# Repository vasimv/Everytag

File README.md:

# Everytag
The firmware emulates Apple Airtag (up to 40 public keys rotating at default 10 minutes interval) and Google Find My Device (just one non-rotating key at the moment). It works on nRF52/54 chips and uses Zephyr. I've tried to optimize power consumption as much as could (microamperes range). MCU's watchdog is used to be sure it always works until battery dies.

One of biggest advantages of the firmware is ability to reconfigure all of its settings via BLE (python script is included), so you can change keys, transmitting power, broadcasting interval and such without reflashing. To minimize power consumption, the firmware accepts connections to change settings only for 2 seconds every minute and has simple password protection.

As beta test feature, it counts current time (if your board has 32.768kHz crystal) and saves current time to the flash periodically, so clock won't drift too much even if it gets reboot.

Also, it is possible to do OTA firmware update on nRF52/54 chips with at least 512KB flash/RRAM memory through mcumgr protocol. That includes nRF52832 (512KB version), nRF52833, nRF54L15. OTA won't work on nRF52805, nRF52810 but you can still change settings through BLE.

## Credits and useful links
Big thanks to OpenHaystack project for their great work: https://github.com/seemoo-lab/openhaystack

The firmware originated as a fork of macless-haystack project and has some of its code: https://github.com/dchristl/macless-haystack

To query locations you can use FindMy scripts: https://github.com/biemster/FindMy

To create Google FMDN key and query locations, use this: https://github.com/leonboe1/GoogleFindMyTools

## Hardware

The firmware has support (see boards/ subdirectory) and tested on these boards and beacons: NRF52DK (nRF52832), NRF54L15DK (nRF54L15), KKM C2 (nRF52805), KKM K4P (K5) with accelerometer (nRF52833), KKM P1 (nRF52810), KKM P11 (nRF52810), Fanstel NRF52805EVM (nRF52805), Minew HCB22E (nRF52832). For NRF52DK, KKM C2 and KKM K4P you will have to use button to turn it on after first flash. On other boards/beacons it'll start right after flashing. Only one LED will blink on the start (1 short, 2 long).

Button (first one on NRF52DK board) can be used to turn off/on. Long press the button until 1 short + 2 long LED flashes to start it on. Same long press for shutdown, it'll do two short flashes and issue sys_poweroff(), less than one microampere in that state. Power on/off status is stored into flash, so it'll stay same after battery replacement (will blink once after installing new battery and return to sleep if was turned off).

Additionally, i've included my design of beacon that has Qi/WPC wireless charging support (nRF52833, BQ51013B, BQ25121A), see hardware/ subdirectory. The goal was to make small and very thin beacon (50x20x2mm with LIR2016 li-ion battery). You can order these assembled on PCBWay https://www.pcbway.com/project/shareproject/Small_and_thin_50x20x2mm_Bluetooth_beacon_with_Qi_WPC_wireless_charging_f97170e6.html (around 35 USD per board).

## Compilation
Zephyr-based nRF Connect SDK 2.8.0 is required to compile the firmware.

myboards.h file has compilation-time settings (like how often switch to settings mode, etc). 

In the Visual Studio Code - click on nrfconnect plugin button, create build configuration for your board. Use following configuration files:

prj-smpsrv.conf - debug (through J-Link RTT interface) version with mcumgr support (for 512KB or bigger flash chips). You can use JlinkRTTViewer to connect and see debug messages on its console.

prj-smpsrv-lowpower.conf - no debug version for lowest power consumption and memory usage, with mcumgr support

prj.conf - debug version without mcumgr support (no mcuboot) for small memory chips - nRF52805, nRF52810, nRF52811

prj-lowpower.conf - no debug version for these chips

For nRF52DK/nrf52832 and nRF54L15DK - use nrf52832dk.overlay / nrf54l15dk.overlay files as "Extra Devicetree overlays"

## Running
It is recommended to erase all flash memory before first run to reset NVS storage where the firmware stores its settings.

Disconnect power source (remove battery) for 10-20 seconds and reconnect again after flashing through SWD or using RTT debug console, nrf chips often switch to high power consumption (up to few milliamps range) after using Jlink RTT interface and software reset doesn't help. So far, i haven't found way to avoid that.

By default, the firmware will start broadcasting dummy iBeacon packets with 7 seconds interval at very low power (-8dBm) with TX power field set as battery voltage (like 31 is 3.1 volts). This broadcast will stop as soon as you load Apple Airtag and/or Google FMDN key.

The beacon will use default MAC address (from MCU's registers programmed at factory) for iBeacon and settings broadcasts. You can figure out the address via debug console or using an BLE scanning app (nrfconnect from Nordic is quite good and free) on a smartphone.

## Changing settings via BLE
Every minute it will switch into settings mode for 2 seconds (configurable) and settings (including keys) can be changed by conn_beacon.py script (requires python 3) or by using android application that AI did generate for me (see below). Note, bluez isn't really perfect stack to work with BLE and the script may have troubles while connecting to the beacon. To fix that, you may try to disable/enable bluetooth or even reboot your computer.

The script is used for:
1. Changing its settings and/or writing current time to the beacon
2. Reading current time from the beacon
3. Switching the beacon into mcumgr OTA mode for one minute

All of these requires password authentication (default password is "abcdefgh", can be changed via settings mode too)

Note, after loading an Airtag key, MAC address in settings mode will be changed, it is recommended to set a specific MAC address for the settings mode when loading an Airtag key. Otherwise, you will have to figure out current MAC address via nrfconnect app or in a similar way.

Examples:
`python3 conn_beacon.py -i e7:93:3a:cc:f6:61 -c e7:93:3a:cc:f6:61 -a abcdefgh -n h45edc78 -f f1e101731f1e1b312272f812e521293a3f484414 -k ~/airtags/016WX1_keyfile -p 2 -g 1 -t 1 -w 1 -d 2`

This will connect to beacon with E7:93:3A:CC:F6:61 MAC address, change password to "h45edc78" load airtag key from 016WX1_keyfile, load FMDN key "f1e101731f1e1b312272f812e521293a3f484414", set maximum TX power (+4 or +8 dBm), allow broadcasting both Airtag and FMDN, switching every 2 seconds. You can omit some settings you don't want to change, only MAC address (-i) and authorization code (-a) is required.

`python3 conn_beacon.py -i e7:93:3a:cc:f6:61 -a h45edc78 -w 1`

This will connect to the beacon and synchronize its clock to current time.

`python3 conn_beacon.py -i e7:93:3a:cc:f6:61 -a h45edc78 -r 1`

This will connect to the beacon and read current time

To use OTA update feature, see flash_beacon.sh and flash_list.sh. Debug/lowpower versions of the mcumgr stuff may be uncompatible between each other, so you may get troubles with reflashing over bluetooth if flashed wrong version first. Settings are stored in separate region of flash/RRAM and they will be same after OTA, use full chip erase through SWD to get rid of old settings or use conn_beacon.py to program new ones.

## Using android application to change settings
Check subdirectory tagcheck for the android application. I have around zero knowledge about the android application development, so ChatGPT did wrote it for me. Sorry for its general ugliness, i'm not an UI guy. This is AndroidStudio project and you can compile it by yourself or use apk included.

"SCAN BLE" functionality will find all BLE stuff with RSSI is bigger than specififed value. This will help to find MAC address of your beacon (place it very close to the phone's bluetooth antenna, so RSSI will be bigger). You can tap on one of scanned results to fill target's MAC address to send settings instead of typing MAC manually.

On settings screen you can choose which settings to update on the Everytag beacon by activating their respective checkboxes. You have to set target MAC address and password (authorization code) to be able to reconfigure beacon. You will need to upload an airtag keyfile to the phone to change its broadcast key.

"Firmware Update" will upgrade firmware through BLE, you have to upload zephyr.signed.bin to your phone first.

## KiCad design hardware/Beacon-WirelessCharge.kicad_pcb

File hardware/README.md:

## Bluetooth beacon design with Qi/WPC charging

The goal of the project was to make thin and small BLE beacon that uses Li-Ion battery and can be recharged with wireless charging. Note, it may not work with all Qi/WPC chargers because small receiving charging coil, it is highly recommended to adapt charger by replacing its transmitting coil with small 20mm diameter coil. I've used Wurth 760308101104 coil with Adafruit 2162 Qi/WPC charger module.

Final size with LIR2016 battery - 50x20x2mm in thin variant. If height is not limited, then battery can be placed above the board and size will be 30x20mm. A ferrite gasket 20x15mm plate is strongly recommended to be glued on the receiving coil, i've used Wurth 74274119 in that role. 5x1mm round magnet can be placed in the hole on the board and transmitting antenna, so both coils will self-align while charge.

When placed on a Qi/WPC charger - reset pulse will be generated for the MCU, keep that in mind if you want to use with your own firmwares. BQ25121A is used in I2C-only configuration to simplify PCB design, you have to configure charging current, voltages and such during MCU initialization.

BQ25121A and 0402 sized components are quite hard to solder manually, so you may want to order them assembled! Link on PCBWay: https://www.pcbway.com/project/shareproject/Small_and_thin_50x20x2mm_Bluetooth_beacon_with_Qi_WPC_wireless_charging_f97170e6.html

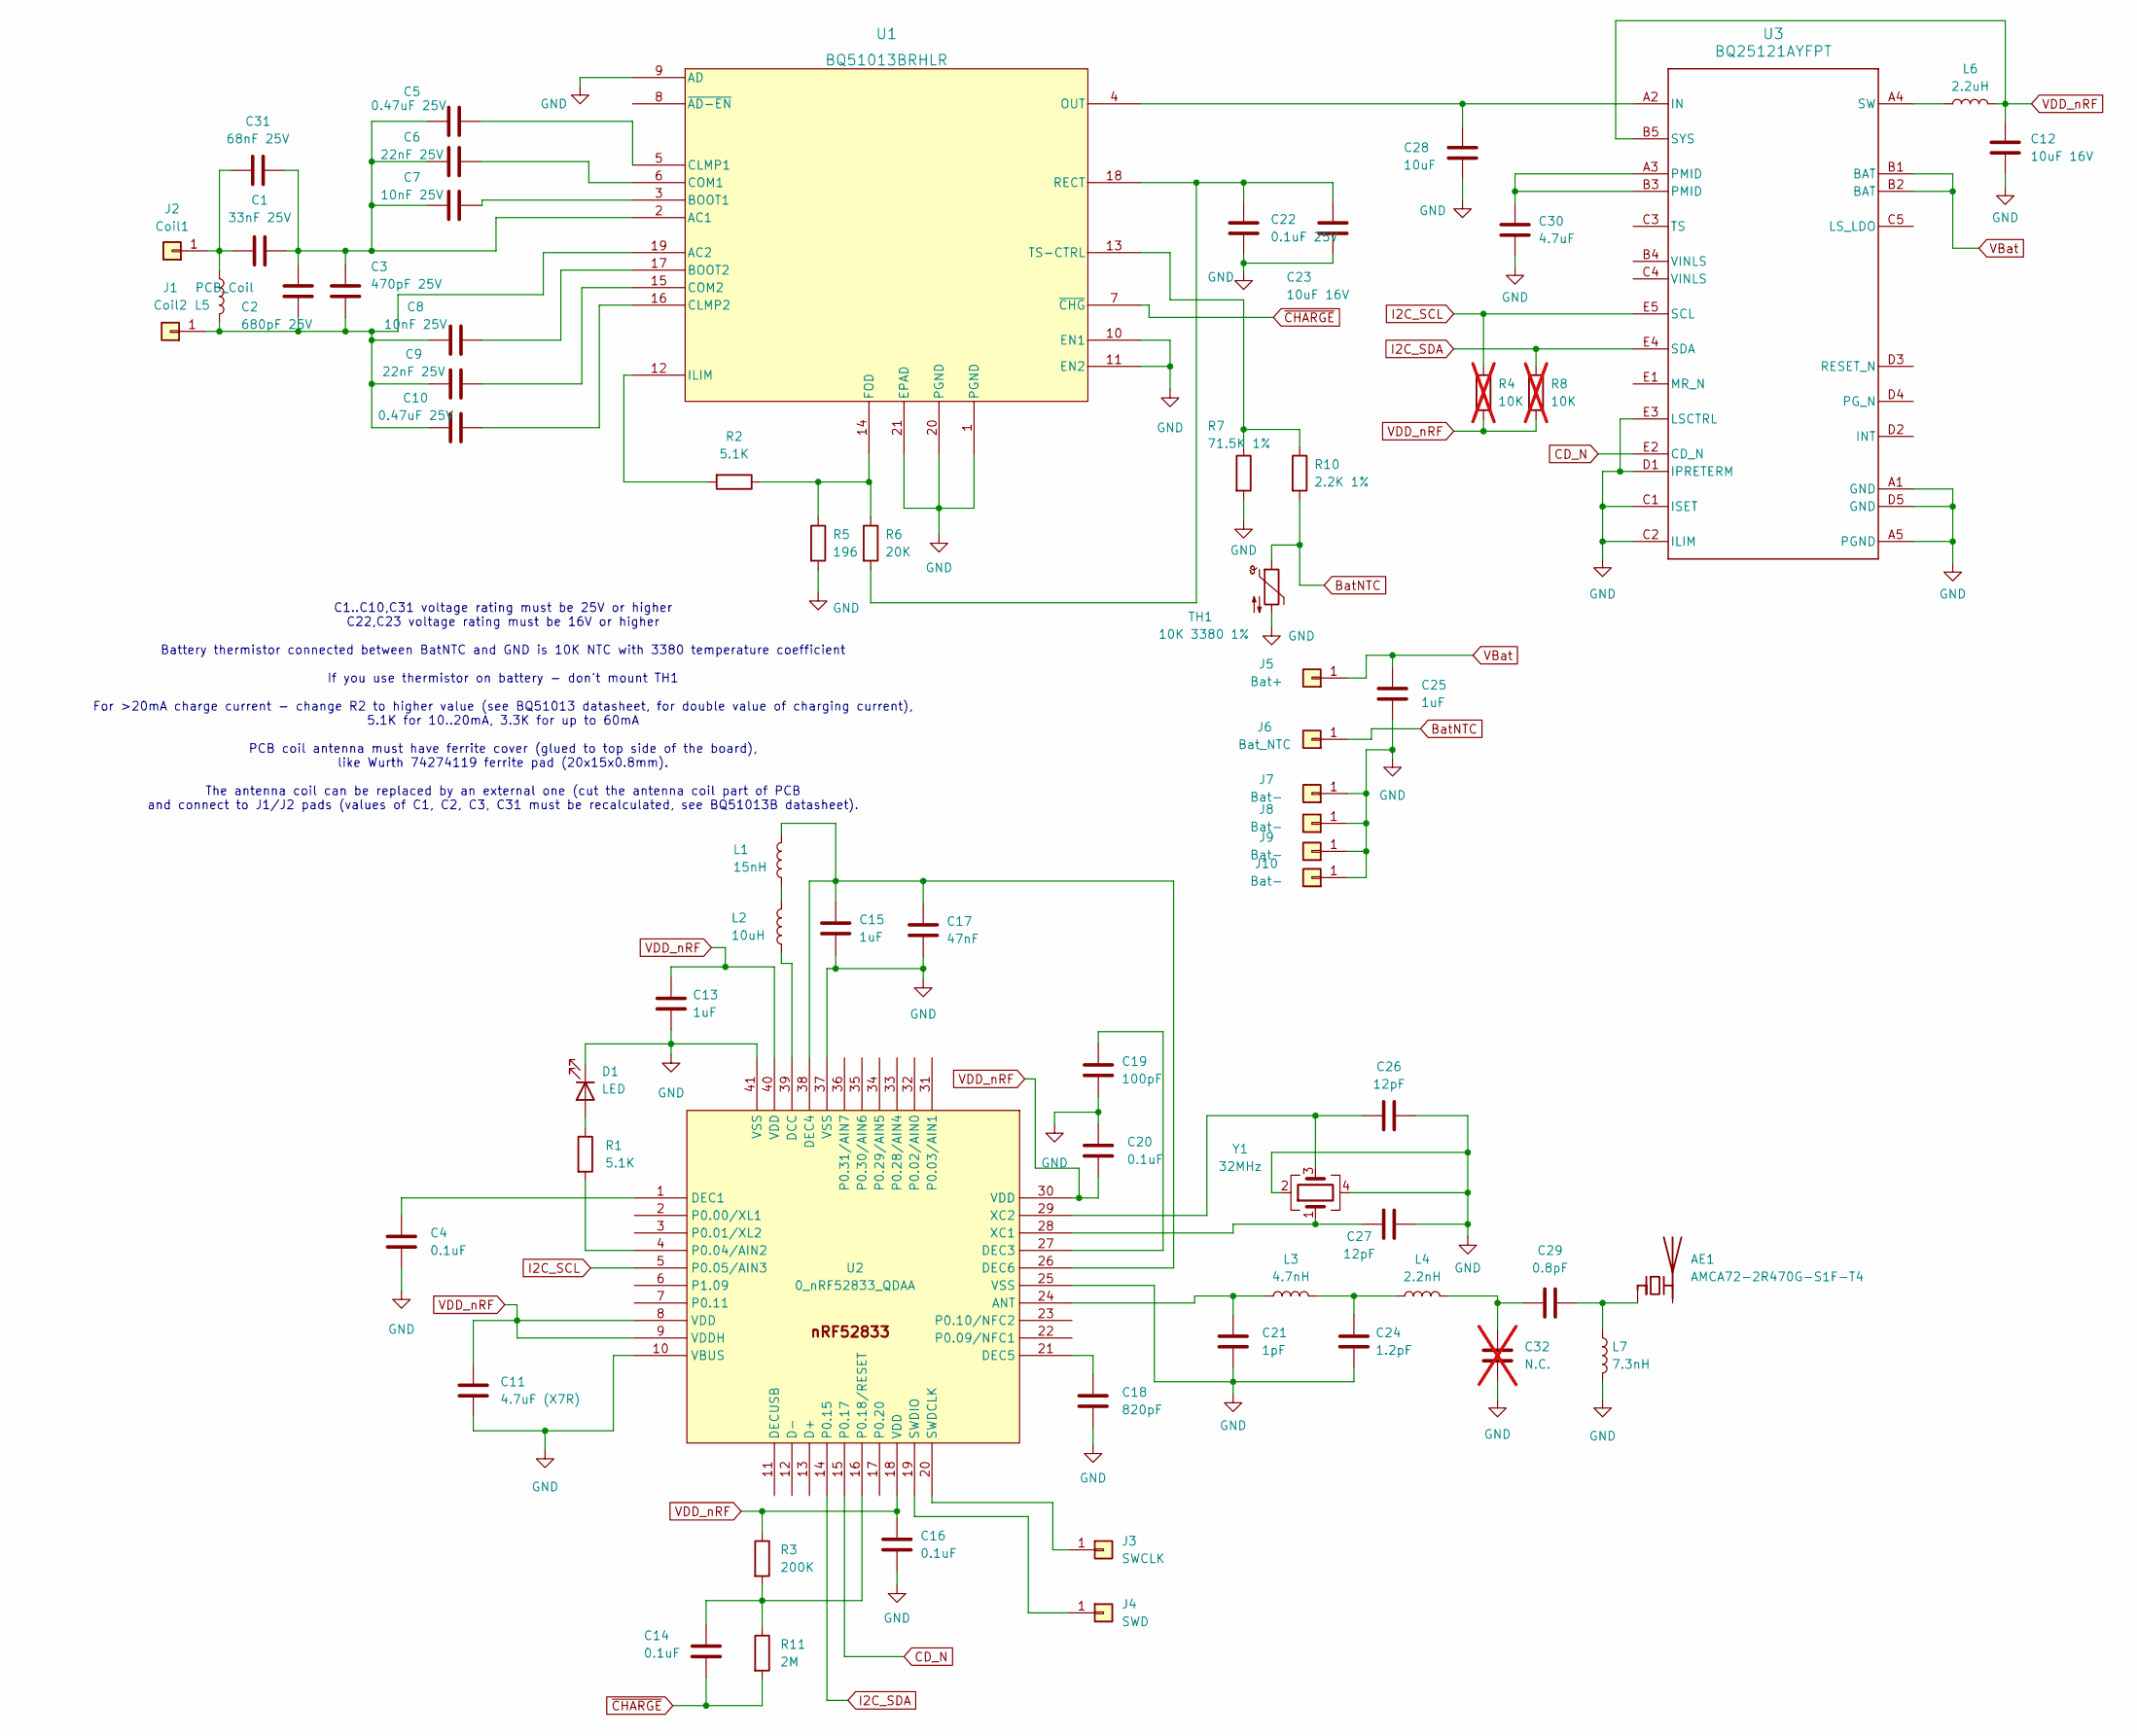
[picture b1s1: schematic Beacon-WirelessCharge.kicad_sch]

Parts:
AE1: AMCA72-2R470G-S1F-T4; Antenna_2450AT43A100
C1: 33nF 25V; C_0402_1005Metric
C2: 680pF 25V; C_0402_1005Metric
C3: 470pF 25V; C_0402_1005Metric
C4, C14, C16, C20: 0.1uF; C_0402_1005Metric
C5, C10: 0.47uF 25V; C_0402_1005Metric
C6, C9: 22nF 25V; C_0402_1005Metric
C7, C8: 10nF 25V; C_0402_1005Metric
C11: 4.7uF (X7R); C_0603_1608Metric
C12, C23: 10uF 16V; C_0603_1608Metric
C13, C15, C25: 1uF; C_0402_1005Metric
C17: 47nF; C_0402_1005Metric
C18: 820pF; C_0402_1005Metric
C19: 100pF; C_0402_1005Metric
C21: 1pF; C_0402_1005Metric
C22: 0.1uF 25V; C_0402_1005Metric
C24: 1.2pF; C_0402_1005Metric
C26, C27: 12pF; C_0402_1005Metric
C28: 10uF; C_0402_1005Metric
C29: 0.8pF; C_0402_1005Metric
C30: 4.7uF; C_0402_1005Metric
C31: 68nF 25V; C_0402_1005Metric
C32: N.C.; C_0402_1005Metric; not fitted
D1: LED; D_0402_1005Metric
J1: Coil2; Pin-1.5_1.5mm
J2: Coil1; Pin-1.5_1.5mm
J3: SWCLK; Pin-1.5_1.5mm
J4: SWD; Pin-1.5_1.5mm
J5: Bat+; Pin-1.5_1.5mm
J6: Bat_NTC; Pin-1.5_1.5mm
J7, J8, J9, J10: Bat-; Pin-1.5_1.5mm
L1: 15nH; L_0402_1005Metric
L2: 10uH; L_0603_1608Metric
L3: 4.7nH; L_0402_1005Metric
L4: 2.2nH; L_0402_1005Metric
L5: PCB_Coil; antenna 19x13mm
L6: 2.2uH; L_0603_1608Metric
L7: 7.3nH; L_0402_1005Metric
R1, R2: 5.1K; R_0402_1005Metric
R3: 200K; R_0402_1005Metric
R4, R8: 10K; R_0402_1005Metric; not fitted
R5: 196; R_0402_1005Metric
R6: 20K; R_0402_1005Metric
R7: 71.5K 1%; R_0402_1005Metric
R10: 2.2K 1%; R_0402_1005Metric
R11: 2M; R_0402_1005Metric
TH1: 10K 3380 1%; R_0402_1005Metric
U1: BQ51013BRHLR; RHL20_2P05X3P05
U2: 0_nRF52833_QDAA; _Applications_test_rsk_lib_RSK-ONLY_Nordic Active DB.DbLib_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; PART NUMBER nRF52833-QDAA
U3: BQ25121AYFPT; BGA25C40P5X5_247X253X50
Y1: 32MHz; Crystal_SMD_2016-4Pin_2.0x1.6mm

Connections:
BatNTC: J6.1, R10.2, TH1.1
CD_N: U2.15 (P0.17), U3.E2 (CD_N)
GND: C4.2, C11.2, C12.2, C13.2, C15.2, C16.2, C17.2, C18.2, C19.2, C20.1, C21.2, C22.2, C23.2, C24.2, C25.2, C26.2, C27.2, C28.2, C30.2, C32.2, D1.1 (K), J7.1, J8.1, J9.1, J10.1, L7.2, R5.2, R7.2, TH1.2, U1.1 (PGND), U1.9 (AD), U1.10 (EN1), U1.11 (EN2), U1.20 (PGND), U1.21 (EPAD), U2.10 (VBUS), U2.25 (VSS), U2.37 (VSS), U2.41 (VSS), U3.A1 (GND), U3.A5 (PGND), U3.C1 (ISET), U3.C2 (ILIM), U3.D1 (IPRETERM), U3.D5 (GND), U3.E3 (LSCTRL), Y1.2, Y1.4
I2C_SCL: R4.1, U2.5 (P0.05/AIN3), U3.E5 (SCL)
I2C_SDA: R8.1, U2.14 (P0.15), U3.E4 (SDA)
unnamed: AE1.1 (FEED), C29.2, L7.1
unnamed: C24.1, L3.2, L4.1
unnamed: C29.1, C32.1, L4.2
unnamed: C30.1, U3.A3 (PMID), U3.B3 (PMID)
unnamed: D1.2 (A), R1.1
unnamed: C2.2, C3.2, C8.1, C9.1, C10.1, J1.1, L5.2, U1.19 (AC2)
unnamed: C1.1, C31.1, J2.1, L5.1
unnamed: J3.1, U2.20 (SWDCLK)
unnamed: J4.1, U2.19 (SWDIO)
unnamed: L1.1, L2.2
unnamed: C1.2, C2.1, C3.1, C5.1, C6.1, C7.1, C31.2, U1.2 (AC1)
unnamed: C7.2, U1.3 (BOOT1)
unnamed: C8.2, U1.17 (BOOT2)
unnamed: C5.2, U1.5 (CLMP1)
unnamed: C10.2, U1.16 (CLMP2)
unnamed: C6.2, U1.6 (COM1)
unnamed: C9.2, U1.15 (COM2)
unnamed: R2.1, R5.1, R6.1, U1.14 (FOD)
unnamed: R2.2, U1.12 (ILIM)
unnamed: C28.1, U1.4 (OUT), U3.A2 (IN)
unnamed: C22.1, C23.1, R6.2, U1.18 (RECT)
unnamed: R7.1, R10.1, U1.13 (TS-CTRL)
unnamed: C21.1, L3.1, U2.24 (ANT)
unnamed: L2.1, U2.39 (DCC)
unnamed: C4.1, U2.1 (DEC1)
unnamed: C19.1, U2.27 (DEC3)
unnamed: C15.1, C17.1, L1.2, U2.26 (DEC6), U2.38 (DEC4)
unnamed: C18.1, U2.21 (DEC5)
unnamed: R1.2, U2.4 (P0.04/AIN2)
unnamed: C14.1, R3.2, R11.1, U2.16 (P0.18/RESET)
unnamed: C27.1, U2.28 (XC1), Y1.1
unnamed: C26.1, U2.29 (XC2), Y1.3
unnamed: L6.1, U3.A4 (SW)
VBat: C25.1, J5.1, U3.B1 (BAT), U3.B2 (BAT)
VDD_nRF: C11.1, C12.1, C13.1, C16.1, C20.2, L6.2, R3.1, R4.2, R8.2, U2.8 (VDD), U2.9 (VDDH), U2.18 (VDD), U2.30 (VDD), U2.40 (VDD), U3.B5 (SYS)
~CHARGE: C14.2, R11.2, U1.7 (~CHG)

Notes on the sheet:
C1..C10,C31 voltage rating must be 25V or higher C22,C23 voltage rating must be 16V or higher Battery thermistor connected between BatNTC and GND is 10K NTC with 3380 temperature coefficient If you use thermistor on battery - don't mount TH1 For >20mA charge current - change R2 to higher value (see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

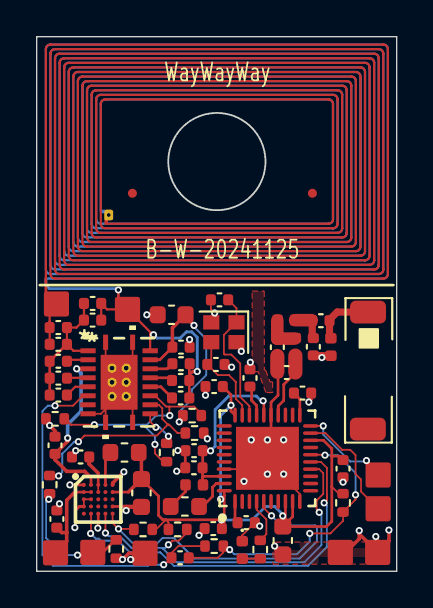
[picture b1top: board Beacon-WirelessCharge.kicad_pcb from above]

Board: 2 copper layers, 20.0 x 29.7 mm, 68 parts (1 on the bottom side), 41 nets.

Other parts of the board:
Fiducial_0.5_1_A, Fiducial_0.5_1_B: Fiducial_0.5mm_Mask1mm

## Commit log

2025-03-09 first version
2025-04-25 Added support for LIS2DW12 accelerometer (KKM K4P beacon), various bugfixes
2025-04-25 added support for Honeycomm HCBB22E (nrf52832 without 32.768kHz quartz)
2025-09-30 Added broadcasting accelerometer data as airtag status byte (see update_status_byte() function), automatic shutdown via ship-mode if no keys programmed on beacons with BQ25121A
2025-10-02 Added config for mcuboot to use RTT console and ignore signature of slot0 image
2025-10-02 If a key defined in public_keys.h (not zero'es) then firmware will use it from start, without need to change settings via bluetooth
2025-10-02 Fixed battery voltage levels for reports
2025-11-09 Added hardware design for nRF52833 based beacon with Qi/WPC wireless charging
2025-12-29 correct verbage
    fairly certain you meant minimize power usage not "maximize"
2026-01-10 Added button support to turn off/on for KKM C2, KKM K4P beacons and nRF52DK board
2026-01-11 Added note about high power consumption after using RTT interface to flash/debug
2026-01-11 Added note about OTA
2026-01-13 Fixed button definition for KKM C2
2026-02-15 Added android application to configure Everytag from a phone
2026-02-17 Added OTA firmware upload through Nordic mcumgr android library.
2026-04-22 Update battery status right away, not waiting key change interval
